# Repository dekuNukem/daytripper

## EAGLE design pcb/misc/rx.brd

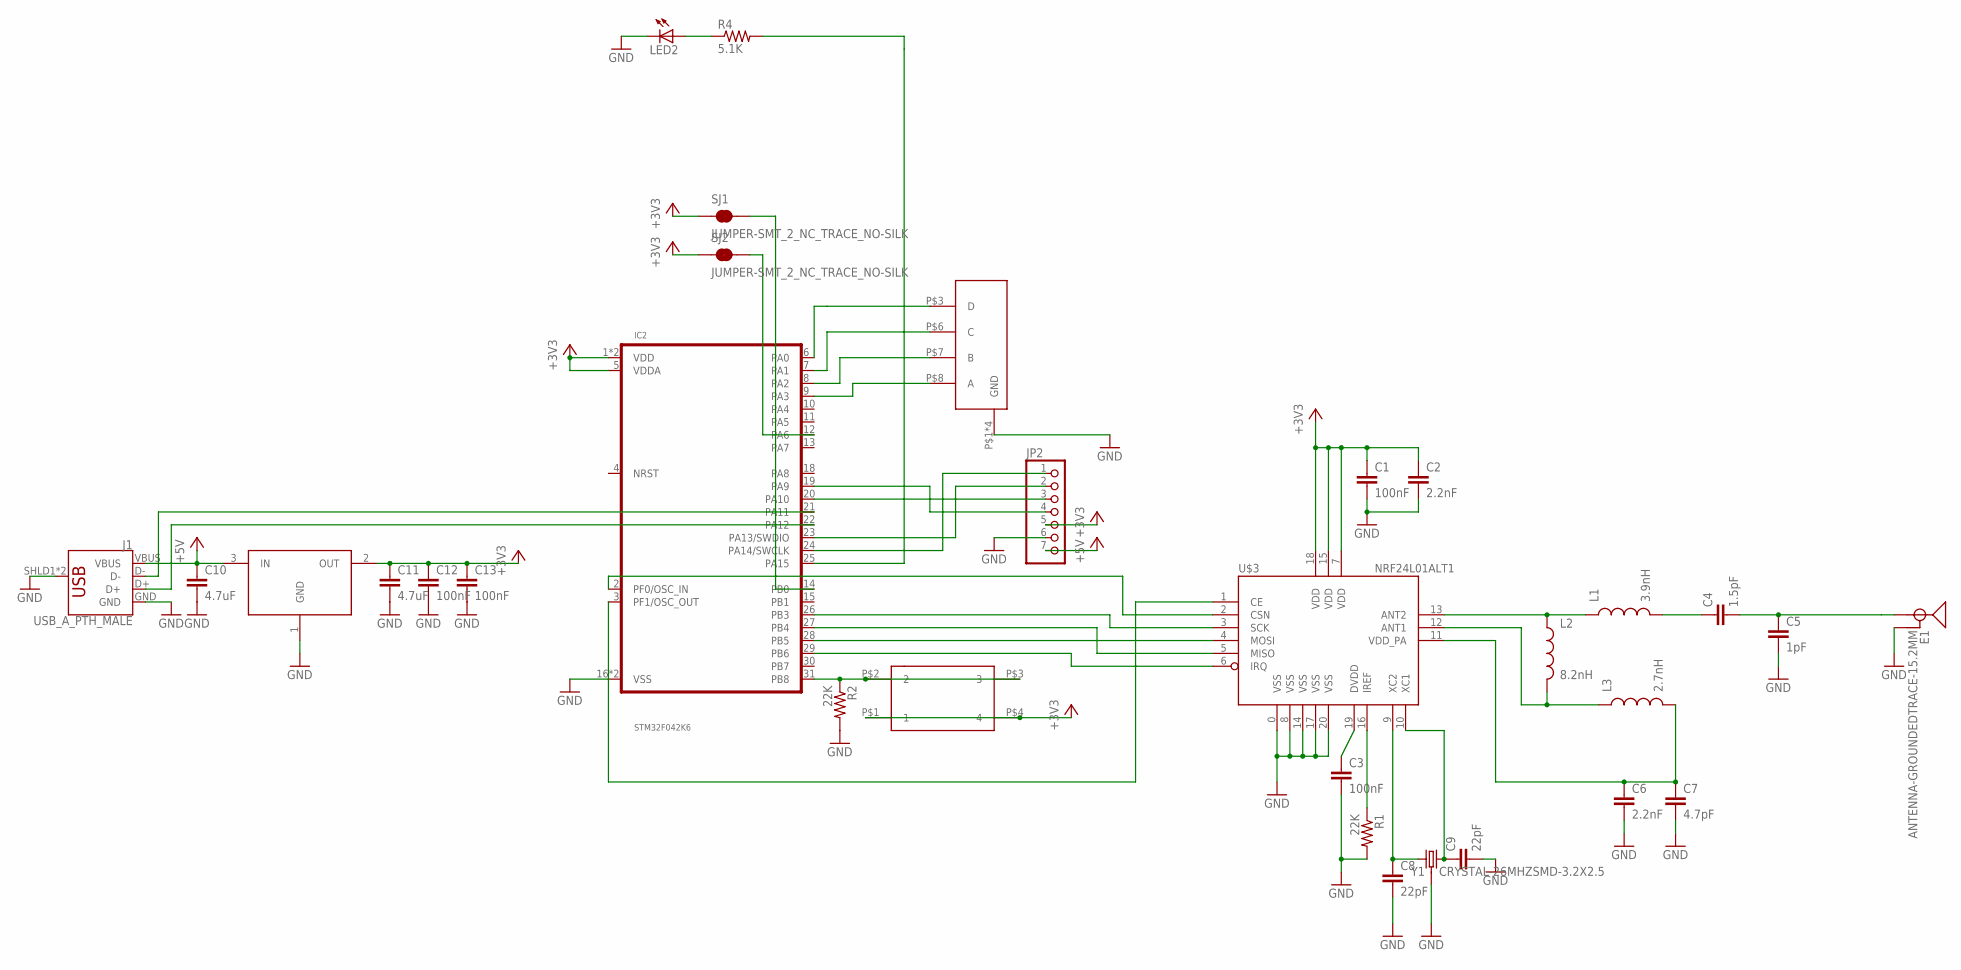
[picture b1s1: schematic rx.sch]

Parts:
C1, C3, C12, C13: 100nF; 0805
C2, C6: 2.2nF; 0805
C4: 1.5pF; 0805
C5: 1pF; 0805
C7: 4.7pF; 0805
C8, C9: 22pF; 0805
C10, C11: 4.7uF; 0805
E1: ANTENNA-GROUNDEDTRACE-15.2MM; TRACE_ANTENNA_2.4GHZ_15.2MM
IC2: STM32F042K6; TQFP32-08
J1: USB_A_PTH_MALE; USB-A-H
JP2: PINHD-1X8CLEANBIG; 1X08-CLEANBIG
L1: 3.9nH; 0805
L2: 8.2nH; 0805
L3: 2.7nH; 0805
LED2: LEDCHIP-LED0805; CHIP-LED0805
R1, R2: 22K; 0805
R4: 5.1K; 0805
SJ1, SJ2: JUMPER-SMT_2_NC_TRACE_NO-SILK; SMT-JUMPER_2_NC_TRACE_NO-SILK
U$1: SW_3POS_DEVSW_3POS_OFFICIAL; SW_3POS_FOOT_OFFICIAL
U$3: NRF24L01ALT1; QFN20_ALT1
U$4: XC6206_DEV; SOT23R_INFINEON
U$10: 324_SW; 342_SWICH_FOOT
Y1: CRYSTAL-26MHZSMD-3.2X2.5; CRYSTAL-SMD-3.2X2.5MM

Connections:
+3V3: C1.1, C2.1, C11.1, C12.1, C13.1, IC2.1 (VDD), IC2.5 (VDDA), IC2.17 (VDD), JP2.5, SJ1.1, SJ2.1, U$3.7 (VDD), U$3.15 (VDD), U$3.18 (VDD), U$4.2 (OUT), U$10.P$1 (1), U$10.P$4 (4)
+5V: C10.1, J1.VBUS, JP2.7, U$4.3 (IN)
GND: C1.2, C2.2, C3.2, C5.2, C6.2, C7.2, C8.2, C9.2, C10.2, C11.2, C12.2, C13.2, E1.GND, IC2.16 (VSS), IC2.32 (VSS), J1.GND, J1.SHLD1 (SHIELD), J1.SHLD2 (SHIELD), JP2.6, LED2.C, R1.2, R2.2, U$1.P$1 (GND), U$1.P$2 (GND), U$1.P$4 (GND), U$1.P$5 (GND), U$3.0 (VSS), U$3.8 (VSS), U$3.14 (VSS), U$3.17 (VSS), U$3.20 (VSS), U$4.1 (GND), Y1.2 (3), Y1.4 (3)
unnamed: C3.1, U$3.19 (DVDD)
unnamed: R1.1, U$3.16 (IREF)
unnamed: L1.1, L2.1, U$3.13 (ANT2)
unnamed: C4.1, L1.2
unnamed: C4.2, C5.1, E1.ANT (SIGNAL)
unnamed: L2.2, L3.1, U$3.12 (ANT1)
unnamed: C8.1, U$3.9 (XC2), Y1.1
unnamed: C6.1, C7.1, L3.2, U$3.11 (VDD_PA)
unnamed: C9.1, U$3.10 (XC1), Y1.3 (2)
unnamed: IC2.6 (PA0), U$1.P$3 (D)
unnamed: IC2.31 (PB8), R2.1, U$10.P$2 (2), U$10.P$3 (3)
unnamed: IC2.21 (PA11), J1.D-
unnamed: IC2.22 (PA12), J1.D+
unnamed: IC2.28 (PB5), U$3.4 (MOSI)
unnamed: IC2.27 (PB4), U$3.5 (MISO)
unnamed: IC2.26 (PB3), U$3.3 (SCK)
unnamed: IC2.29 (PB6), U$3.6 (IRQ)
unnamed: LED2.A, R4.1
unnamed: IC2.2 (PF0/OSC_IN), U$3.2 (CSN)
unnamed: IC2.3 (PF1/OSC_OUT), U$3.1 (CE)
unnamed: IC2.24 (PA14/SWCLK), JP2.1
unnamed: IC2.23 (PA13/SWDIO), JP2.2
unnamed: IC2.20 (PA10), JP2.3
unnamed: IC2.19 (PA9), JP2.4
unnamed: IC2.7 (PA1), U$1.P$6 (C)
unnamed: IC2.8 (PA2), U$1.P$7 (B)
unnamed: IC2.9 (PA3), U$1.P$8 (A)
unnamed: IC2.25 (PA15), R4.2
unnamed: IC2.12 (PA6), SJ2.2
unnamed: IC2.14 (PB0), SJ1.2

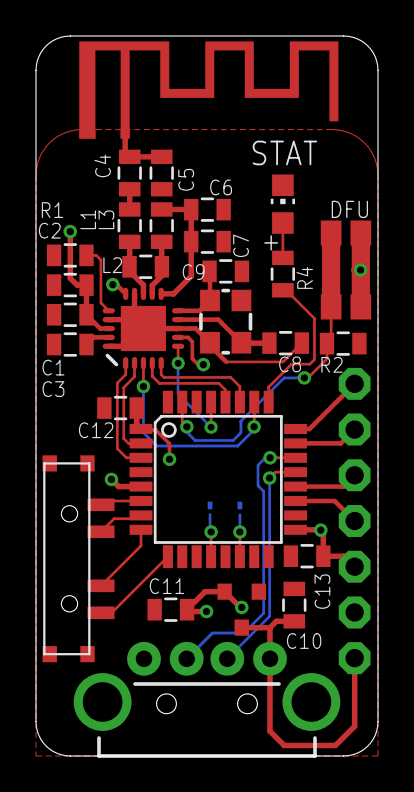
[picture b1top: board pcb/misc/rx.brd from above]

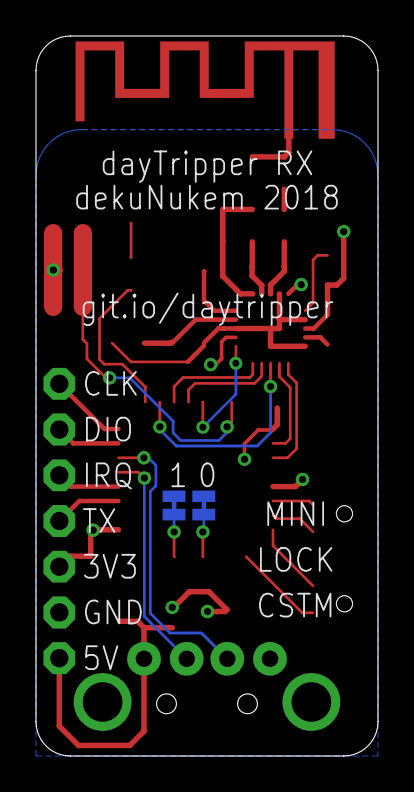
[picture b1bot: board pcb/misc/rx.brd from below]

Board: 2 copper layers, 19.0 x 40.0 mm, 31 parts (2 on the bottom side), 33 nets.

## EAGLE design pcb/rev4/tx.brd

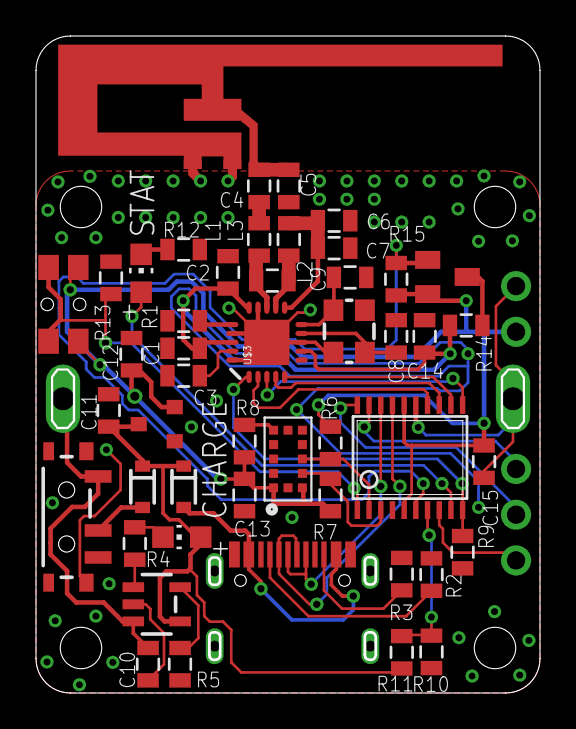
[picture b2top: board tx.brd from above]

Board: 2 copper layers, 28.0 x 36.5 mm, 55 parts (1 on the bottom side), 40 nets.

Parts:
BT1: TX_SPARKFUN-BATTERIES_BATTCON_24.5MM_PTH
C1, C2, C10, C11, C12, C14: 4.7uF; 0805
C3, C13, C15: 100nF; 0805
C4: 1.5pF; 0805
C5: 1pF; 0805
C6: 2.2nF; 0805
C7: 4.7pF; 0805
C8, C9: 22pF; 0805
D1, D2: BAT20J; SOD-323
E1: ANTENNA; TRACE_ANTENNA_2.4GHZ_25.7MM_TUNED
JP1: 1X03-CLEANBIG
L1: 3.9nH; 0805
L2: 8.2nH; 0805
L3: 2.7nH; 0805
LED1, LED2: CHIP-LED0805
Q1: BSS84; SOT23
R1, R5, R8, R9, R10, R11, R13, R15: 22K; 0805
R2, R3, R4, R6, R7, R12: 5.1K; 0805
R14: 1 Ohm; 0805
S2: SWITCH-SPST-SMD-A
U1: LGA12_ST
U3: MCP73831T-2ACI/OT; SOT23-5
U$1, U$12, U$13, U$14: M2_SCREW_DEV; M2_SCREW_FOOT
U$2: STM32F030F4; TSSOP20
U$3: NRF24L01ALT1; QFN20_ALT1
U$4: USBC_16P; USBC_16P_FOOT
U$9: XC6206_DEV; SOT23R_INFINEON
U$10: 324_SW324_SWITCH_FOOT_HOLE; 342_SWICH_FOOT_HOLE
U$11: PINHD1X2; 1X02
Y1: CRYSTAL-26MHZSMD-3.2X2.5; CRYSTAL-SMD-3.2X2.5MM

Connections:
+3V3: C12.1, C13.1, C15.1, Q1.2, R6.2, R7.2, R8.2, R15.1, U1.1, U1.11, U$2.5, U$2.16, U$9.2, U$10.P$1, U$10.P$4, U$11.1
GND: BT1.2, C1.2, C2.2, C3.2, C5.2, C6.2, C7.2, C8.2, C9.2, C10.2, C11.2, C12.2, C13.2, C14.2, C15.2, E1.GND, E1.GND2, R1.2, R2.2, R3.2, R5.2, R9.2, R11.1, R12.1, R13.2, S2.G1, S2.G2, S2.G3, S2.G4, U1.2, U1.3, U1.4, U1.6, U1.12, U3.2, U$2.15, U$3.0, U$3.8, U$3.14, U$3.17, U$3.20, U$4.A1B12, U$4.B11A12, U$4.P$13, U$4.P$14, U$4.P$15, U$4.P$16, U$9.1, U$11.2, Y1.2, Y1.4
unnamed: C3.1, U$3.19
unnamed: R1.1, U$3.16
unnamed: L1.1, L2.1, U$3.13
unnamed: C4.1, L1.2
unnamed: C4.2, C5.1, E1.ANT
unnamed: L2.2, L3.1, U$3.12
unnamed: C8.1, U$3.9, Y1.1
unnamed: C6.1, C7.1, L3.2, U$3.11
unnamed: C9.1, U$3.10, Y1.3
unnamed: R3.1, U$4.B5
unnamed: R2.1, U$4.A5
unnamed: LED1.C, R4.1
unnamed: R4.2, U3.1
unnamed: U$2.13, U$3.4
unnamed: U$2.12, U$3.5
unnamed: U$2.11, U$3.3
unnamed: R5.1, U3.5
unnamed: U$2.18, U$4.A6, U$4.B6
unnamed: D2.A, S2.2
unnamed: U$2.14, U$3.2
unnamed: R9.1, U$2.10, U$3.1
unnamed: R7.1, U1.10, U$2.3
unnamed: R6.1, U1.9, U$2.2
unnamed: R8.1, U1.5
unnamed: BT1.1, C10.1, S2.3, U3.3
unnamed: D1.A, U$4.A4B9, U$4.B4A9
unnamed: C11.1, D1.C, D2.C, LED1.A, R10.2, U3.4, U$9.3
unnamed: LED2.C, R12.2
unnamed: LED2.A, U$2.9
unnamed: R13.1, U$2.1, U$10.P$2, U$10.P$3
unnamed: JP1.3, U$2.19
unnamed: JP1.2, U$2.20
unnamed: JP1.1, U$2.8
unnamed: U$2.17, U$4.A7, U$4.B7
unnamed: R10.1, R11.2, U$2.7
unnamed: C1.1, C2.1, C14.1, R14.2, U$3.7, U$3.15, U$3.18
unnamed: Q1.3, R14.1
unnamed: Q1.1, R15.2, U$2.6

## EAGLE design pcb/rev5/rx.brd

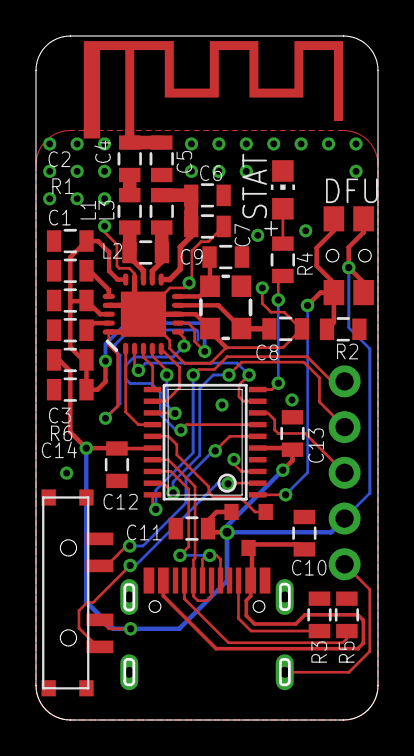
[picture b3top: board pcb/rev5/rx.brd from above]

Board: 2 copper layers, 19.0 x 38.0 mm, 34 parts (1 on the bottom side), 32 nets.

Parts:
C1, C2, C10, C11, C14: 4.7uF; 0805
C3, C12, C13: 100nF; 0805
C4: 1.5pF; 0805
C5: 1pF; 0805
C6: 2.2nF; 0805
C7: 4.7pF; 0805
C8, C9: 12pF; 0805
E1: ANTENNA-GROUNDEDTRACE-15.2MM; TRACE_ANTENNA_2.4GHZ_15.2MM
IC1: STM32F042F4; TSSOP20
IC2: NRF24L01ALT1; QFN20_ALT1
L1: 3.9nH; 0805
L2: 8.2nH; 0805
L3: 2.7nH; 0805
LED1: CHIP-LED0805
R1, R2: 22K; 0805
R3, R4, R5: 5.1K; 0805
R6: 1 Ohm; 0805
SW1: SW_3POS_DEVSW_3POS_OFFICIAL; SW_3POS_FOOT_OFFICIAL
SW2: 324_SW324_SWITCH_FOOT_HOLE; 342_SWICH_FOOT_HOLE
TP2: TPTP12R; TP12R
U1: USBC_16P; USBC_16P_FOOT
U2: XC6206_DEV; SOT23R_INFINEON
U$5: PINHD5; 1X05
Y1: 16MHz_12pF; CRYSTAL-SMD-3.2X2.5MM

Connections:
+3V3: C11.1, C12.1, C13.1, IC1.5, IC1.16, R6.1, SW1.P$7, SW2.P$1, SW2.P$4, U2.2, U$5.4
+5V: C10.1, U1.A4B9, U1.B4A9, U2.3
GND: C1.2, C2.2, C3.2, C5.2, C6.2, C7.2, C8.2, C9.2, C10.2, C11.2, C12.2, C13.2, C14.2, E1.GND, IC1.15, IC2.0, IC2.8, IC2.14, IC2.17, IC2.20, LED1.C, R1.2, R2.2, R3.2, R5.2, SW1.P$1, SW1.P$2, SW1.P$4, SW1.P$5, U1.A1B12, U1.B11A12, U1.P$13, U1.P$14, U1.P$15, U1.P$16, U2.1, U$5.5, Y1.2, Y1.4
unnamed: C3.1, IC2.19
unnamed: IC2.16, R1.1
unnamed: IC2.13, L1.1, L2.1
unnamed: C4.1, L1.2
unnamed: C4.2, C5.1, E1.ANT
unnamed: IC2.12, L2.2, L3.1
unnamed: C8.1, IC2.9, Y1.1
unnamed: C6.1, C7.1, IC2.11, L3.2
unnamed: C9.1, IC2.10, Y1.3
unnamed: IC1.2, SW1.P$8
unnamed: IC1.1, R2.1, SW2.P$2, SW2.P$3
unnamed: IC1.17, U1.A7, U1.B7
unnamed: IC1.18, U1.A6, U1.B6
unnamed: IC1.12, IC2.5
unnamed: IC1.13, IC2.4
unnamed: IC1.11, IC2.3
unnamed: IC1.19, U$5.2
unnamed: LED1.A, R4.1
unnamed: IC1.3, TP2.TP
unnamed: IC1.20, U$5.1
unnamed: IC1.8, U$5.3
unnamed: IC1.14, IC2.1
unnamed: IC1.10, R4.2
unnamed: IC1.9, IC2.2
unnamed: R3.1, U1.B5
unnamed: IC1.6, SW1.P$6
unnamed: R5.1, U1.A5
unnamed: C1.1, C2.1, C14.1, IC2.7, IC2.15, IC2.18, R6.2
unnamed: IC1.7, IC2.6

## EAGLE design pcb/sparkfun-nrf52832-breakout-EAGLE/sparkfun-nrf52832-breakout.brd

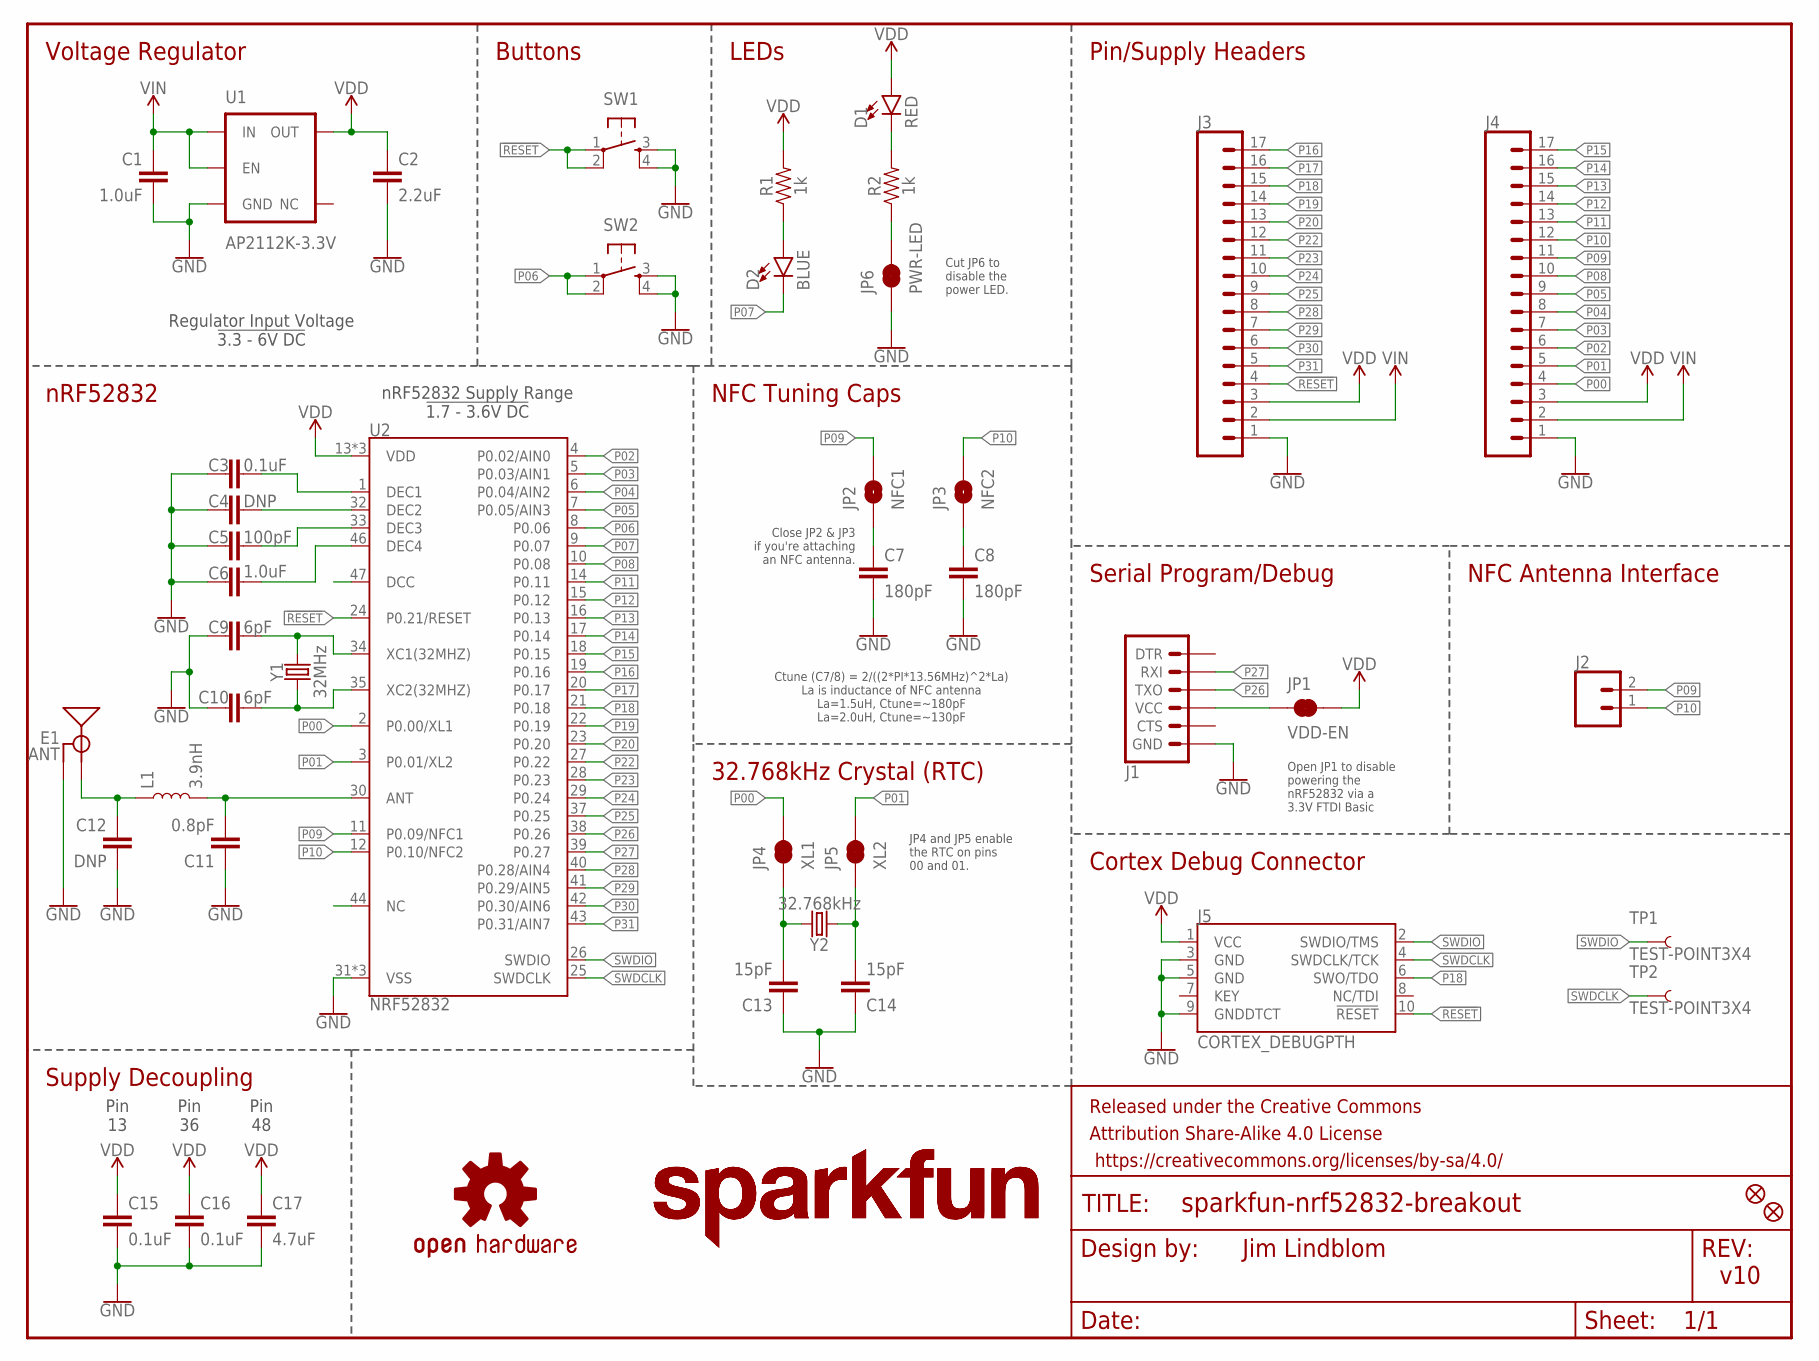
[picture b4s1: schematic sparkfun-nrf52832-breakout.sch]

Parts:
C1: 1.0uF; 0603
C2: 2.2uF; 0603
C3, C15, C16: 0.1uF; 0402
C4, C12: DNP; 0402
C5: 100pF; 0402
C6: 1.0uF; 0402
C7, C8: 180pF; 0603
C9, C10: 6pF; 0402
C11: 0.8pF; 0402
C13, C14: 15pF; 0402
C17: 4.7uF; 0603
D1: RED; LED-0603
D2: BLUE; LED-0603
E1: ANT; TRACE_ANTENNA_2.4GHZ_15.2MM
FD1, FD2: FIDUCIALUFIDUCIAL; FIDUCIAL-MICRO
FRAME1: FRAME-LETTER; CREATIVE_COMMONS
J1: ARDUINO_SERIAL_PROGRAMPTH; 1X06
J2: CONN_02PTH; 1X02
J3, J4: CONN_17; 1X17
J5: CORTEX_DEBUGPTH; 2X5-PTH-1.27MM
JP1: VDD-EN; SMT-JUMPER_2_NC_TRACE_SILK
JP2: NFC1; SMT-JUMPER_2_NO_SILK
JP3: NFC2; SMT-JUMPER_2_NO_SILK
JP4: XL1; PAD-JUMPER-2-NC_BY_TRACE_YES_SILK
JP5: XL2; PAD-JUMPER-2-NC_BY_TRACE_YES_SILK
JP6: PWR-LED; PAD-JUMPER-2-NC_BY_TRACE_YES_SILK
L1: 3.9nH; 0402
LOGO1: OSHW-LOGOMINI; OSHW-LOGO-MINI
LOGO2, LOGO3: SFE_LOGO_NAME.1_INCH; SFE_LOGO_NAME_.1
R1, R2: 1k; 0603
SW1, SW2: SWITCH_SPST_4_PINRECT; TACTILE_SWITCH_SMD_4.6X2.8MM
TP1, TP2: TEST-POINT3X4; PAD.03X.04
U1: AP2112K-3.3V; SOT23-5
U2: NRF52832; QFN48-6X6MM
Y1: 32MHz; CRYSTAL-SMD-2.0X1.6MM
Y2: 32.768kHz; CRYSTAL-SMD-3.2X1.5MM

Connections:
!RESET!: J3.4, J5.10 (!RESET), SW1.1, SW1.2, U2.24 (P0.21/RESET)
ANT: C11.2, L1.2, U2.30 (ANT)
DCC: U2.47 (DCC)
DEC1: C3.2, U2.1 (DEC1)
DEC2: C4.2, U2.32 (DEC2)
DEC3: C5.2, U2.33 (DEC3)
DEC4: C6.2, U2.46 (DEC4)
GND: C1.2, C2.2, C3.1, C4.1, C5.1, C6.1, C7.2, C8.2, C9.1, C10.2, C11.1, C12.2, C13.1, C14.1, C15.2, C16.2, C17.2, E1.GND, J1.6 (GND), J3.1, J4.1, J5.3 (GND), J5.5 (GND), J5.9 (GNDDTCT), JP6.1, SW1.3, SW1.4, SW2.3, SW2.4, U1.2 (GND), U2.31 (VSS), U2.45 (VSS), U2.EP (VSS)
unnamed: JP6.2, R2.1
unnamed: C13.2, JP4.1, Y2.P$2 (2)
unnamed: C14.2, JP5.1, Y2.P$1 (1)
unnamed: C12.1, E1.ANT (SIGNAL), L1.1
unnamed: D1.C, R2.2
unnamed: J1.4 (VCC), JP1.1
unnamed: D2.A, R1.1
NC: U2.44 (NC)
NFC1: C7.1, JP2.1
NFC2: C8.1, JP3.1
P00: J4.4, JP4.2, U2.2 (P0.00/XL1)
P01: J4.5, JP5.2, U2.3 (P0.01/XL2)
P02: J4.6, U2.4 (P0.02/AIN0)
P03: J4.7, U2.5 (P0.03/AIN1)
P04: J4.8, U2.6 (P0.04/AIN2)
P05: J4.9, U2.7 (P0.05/AIN3)
P06: SW2.1, SW2.2, U2.8 (P0.06)
P07: D2.C, U2.9 (P0.07)
P08: J4.10, U2.10 (P0.08)
P09: J2.2, J4.11, JP2.2, U2.11 (P0.09/NFC1)
P10: J2.1, J4.12, JP3.2, U2.12 (P0.10/NFC2)
P11: J4.13, U2.14 (P0.11)
P12: J4.14, U2.15 (P0.12)
P13: J4.15, U2.16 (P0.13)
P14: J4.16, U2.17 (P0.14)
P15: J4.17, U2.18 (P0.15)
P16: J3.17, U2.19 (P0.16)
P17: J3.16, U2.20 (P0.17)
P18: J3.15, J5.6 (SWO/TDO), U2.21 (P0.18)
P19: J3.14, U2.22 (P0.19)
P20: J3.13, U2.23 (P0.20)
P22: J3.12, U2.27 (P0.22)
P23: J3.11, U2.28 (P0.23)
P24: J3.10, U2.29 (P0.24)
P25: J3.9, U2.37 (P0.25)
P26: J1.3 (TXO), U2.38 (P0.26)
P27: J1.2 (RXI), U2.39 (P0.27)
P28: J3.8, U2.40 (P0.28/AIN4)
P29: J3.7, U2.41 (P0.29/AIN5)
P30: J3.6, U2.42 (P0.30/AIN6)
P31: J3.5, U2.43 (P0.31/AIN7)
SWDCLK: J5.4 (SWDCLK/TCK), TP2.P$1, U2.25 (SWDCLK)
SWDIO: J5.2 (SWDIO/TMS), TP1.P$1, U2.26 (SWDIO)
VDD: C2.1, C15.1, C16.1, C17.1, D1.A, J3.3, J4.3, J5.1 (VCC), JP1.2, R1.2, U1.5 (OUT), U2.13 (VDD), U2.36 (VDD), U2.48 (VDD)
VIN: C1.1, J3.2, J4.2, U1.1 (IN), U1.3 (EN)
XC1: C9.2, U2.34 (XC1(32MHZ)), Y1.3 (2)
XC2: C10.1, U2.35 (XC2(32MHZ)), Y1.1

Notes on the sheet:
Pin 13
Pin 36
Pin 48
v10
Jim Lindblom
Ctune (C7/8) = 2/((2*PI*13.56MHz)^2*La) La is inductance of NFC antenna La=1.5uH, Ctune=~180pF La=2.0uH, Ctune=~130pF
Voltage Regulator
Buttons
LEDs
Pin/Supply Headers
nRF52832
32.768kHz Crystal (RTC)
Supply Decoupling
NFC Tuning Caps
Cortex Debug Connector
Serial Program/Debug
NFC Antenna Interface
Open JP1 to disable powering the nRF52832 via a 3.3V FTDI Basic
Close JP2 & JP3 if you're attaching an NFC antenna.
JP4 and JP5 enable the RTC on pins 00 and 01.
Regulator Input Voltage !3.3 - 6V DC!
nRF52832 Supply Range !1.7 - 3.6V DC!
Cut JP6 to disable the power LED.

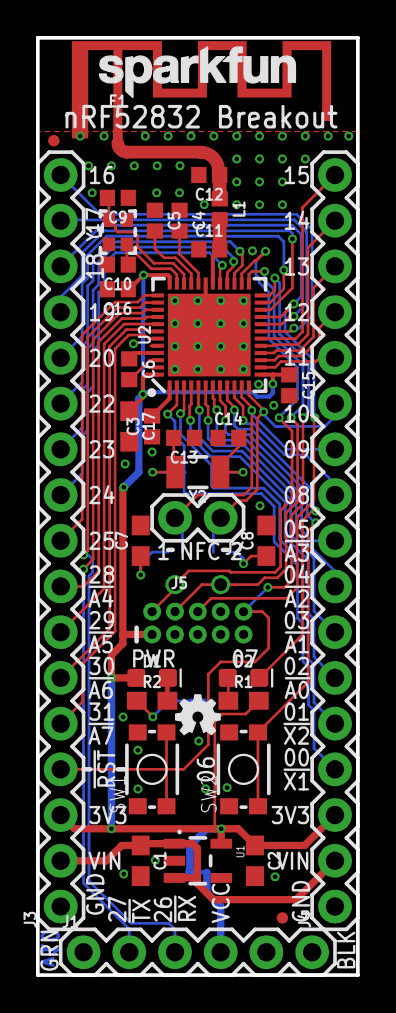
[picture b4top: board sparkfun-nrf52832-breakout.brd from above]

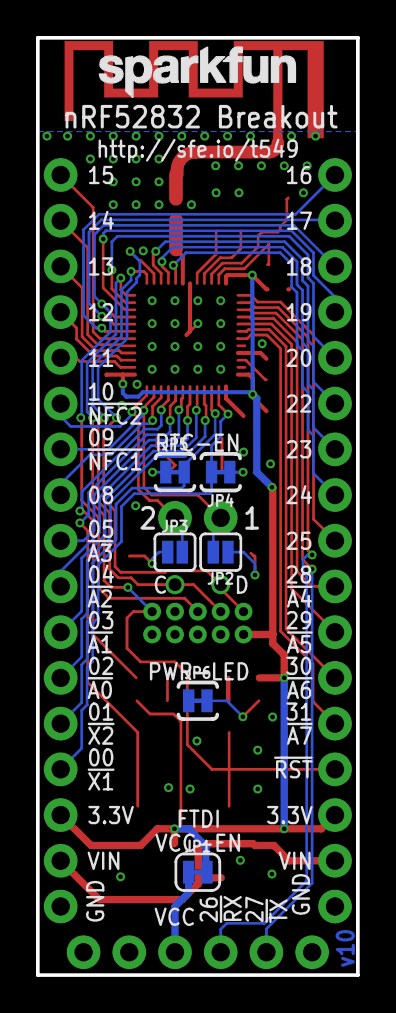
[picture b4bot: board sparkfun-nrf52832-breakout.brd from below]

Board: 2 copper layers, 17.8 x 52.1 mm, 48 parts (9 on the bottom side), 53 nets.

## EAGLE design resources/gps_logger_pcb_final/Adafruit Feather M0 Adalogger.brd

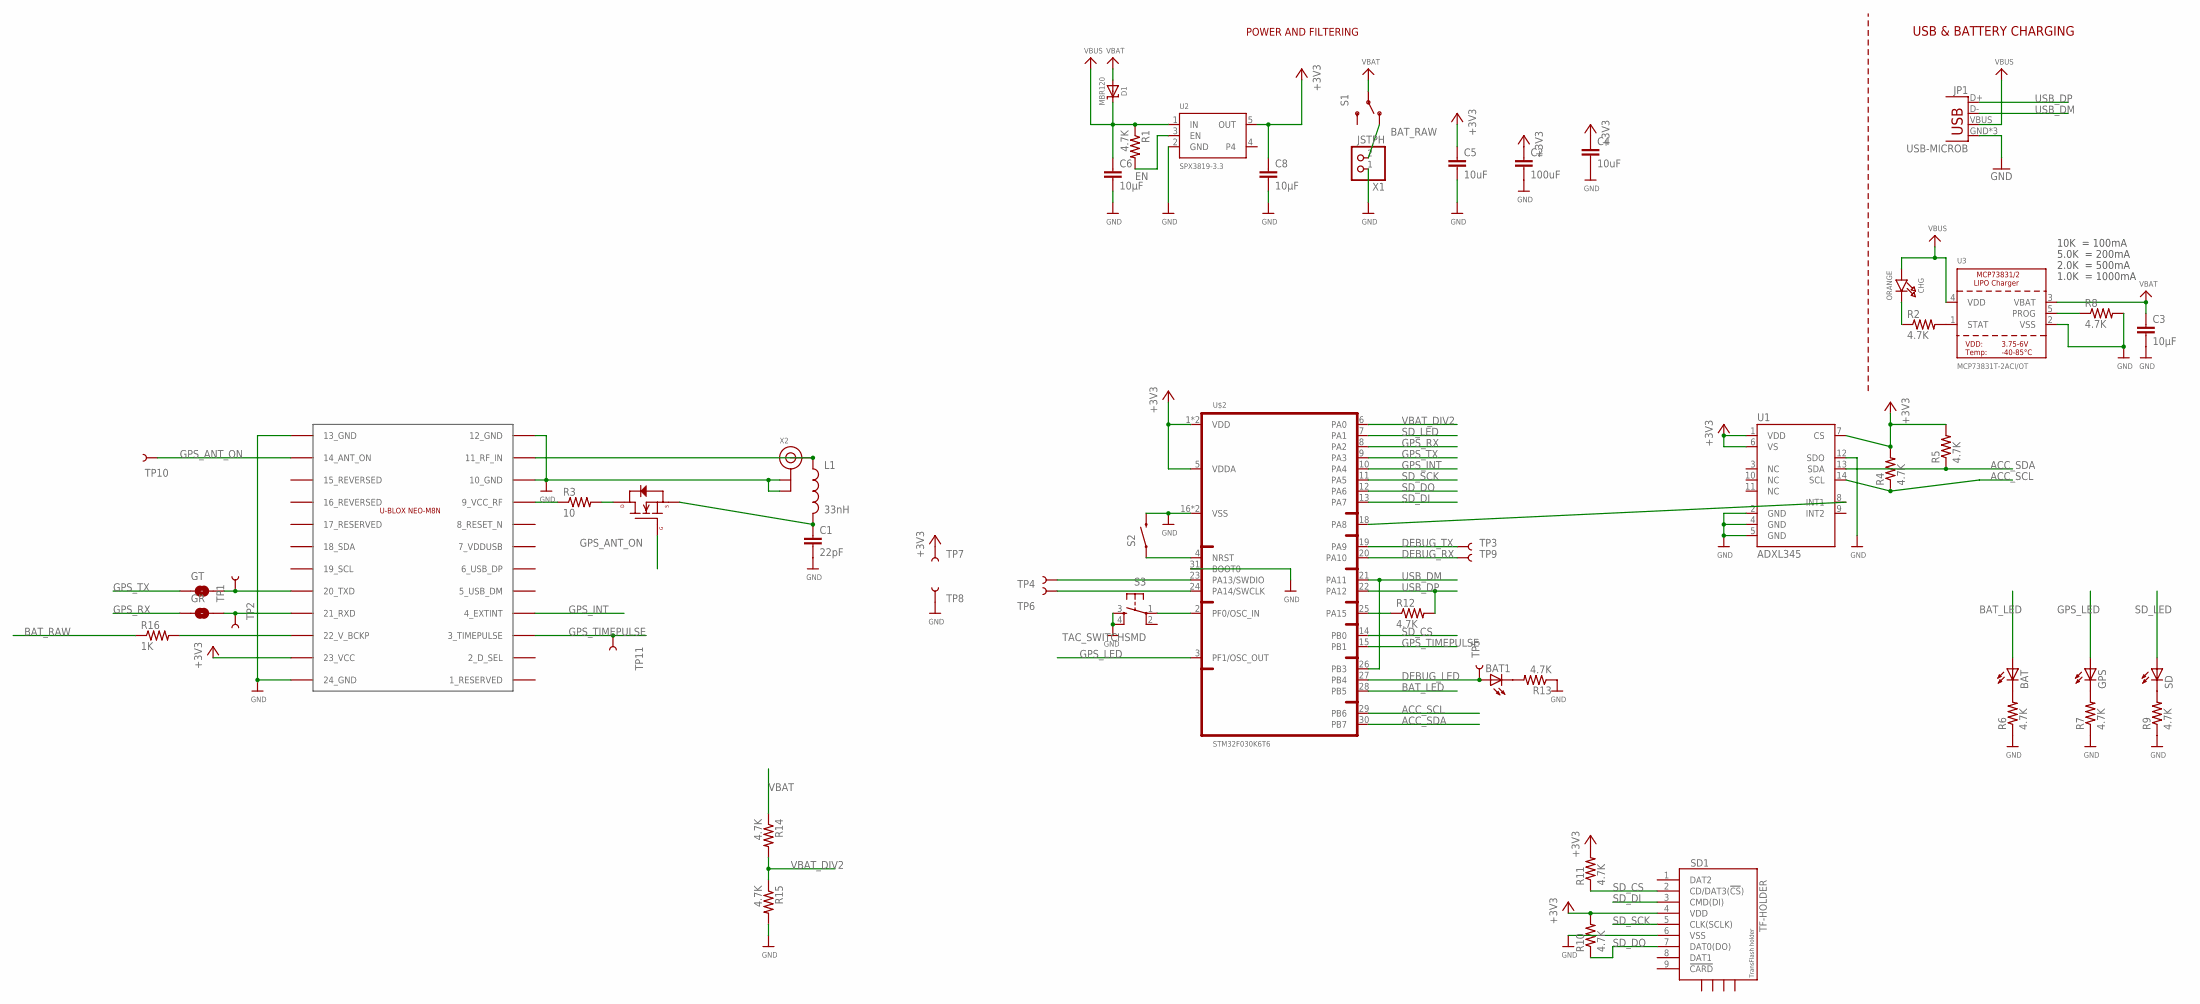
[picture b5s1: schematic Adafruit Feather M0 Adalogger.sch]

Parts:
BAT, BAT1: LEDCHIPLED_0805; CHIPLED_0805
C1: 22pF; 0805
C2: 100uF; 1210
C3, C6, C8: 10µF; 0805
C4, C5: 10uF; 0805
CHG: ORANGE; CHIPLED_0805_NOOUTLINE
D1: MBR120; SOD-123
DEKU1: UBLOX_NEO-M8N
GPS: LEDCHIPLED_0805; CHIPLED_0805
GR: JUMPER-PAD-2-NO; PAD-JUMPER-2-NO_NO_SILK
GT: JUMPER-PAD-2-NO; PAD-JUMPER-2-NO_NO_SILK
JP1: USB-MICROB
L1: 33nH; 0805
R1, R2, R4, R5, R6, R7, R8, R9, R10, R11, R12, R13, R14, R15: 4.7K; 0805
R3: 10; 0805
R16: 1K; 0805
S1: SWITCH-SPDT-SMD-A; SWITCH-SPST-SMD-A
S2: SWITCH-MOMENTARY-2TURTLE; KMR2
S3: TAC_SWITCHSMD; TACTILE-SWITCH-SMD
SD: LEDCHIPLED_0805; CHIPLED_0805
SD1: TF-HOLDER; TF-PULL
TP1, TP2, TP3, TP4, TP5, TP6, TP7, TP8, TP9, TP10, TP11: TEST-POINT3X5; PAD.03X.05
U1: ADXL345; LGA14
U2: SPX3819-3.3; SOT23-5
U3: MCP73831T-2ACI/OT; SOT23-5
U$2: STM32F030K6T6; TQFP32-08
U$24: N-CHANNEL-MOSFET-BSS138; SOT23-3
X1: JSTPH; JSTPH2
X2: ANTENNA_U.FL; U.FL

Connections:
+3V3: C2.1, C4.1, C5.1, C8.1, DEKU1.23_VCC, R4.2, R5.2, R10.2, R11.2, SD1.4 (VDD), TP7.P$1, U1.1 (VDD), U1.6 (VS), U1.7 (CS), U2.5 (OUT), U$2.1 (VDD), U$2.5 (VDDA), U$2.17 (VDD)
ACC_SCL: R4.1, U1.14 (SCL), U$2.29 (PB6)
ACC_SDA: R5.1, U1.13 (SDA), U$2.30 (PB7)
BAT_LED: BAT.A, U$2.28 (PB5)
BAT_RAW: R16.1, S1.1 (O), X1.2
DEBUG_LED: BAT1.A, TP5.P$1, U$2.27 (PB4)
DEBUG_RX: TP9.P$1, U$2.20 (PA10)
DEBUG_TX: TP3.P$1, U$2.19 (PA9)
EN: R1.2, U2.3 (EN)
GND: C1.2, C2.2, C3.2, C4.2, C5.2, C6.2, C8.2, DEKU1.10_GND, DEKU1.12_GND, DEKU1.13_GND, DEKU1.24_GND, JP1.GND, JP1.MT1 (GND), JP1.MT2 (GND), R6.1, R7.1, R8.2, R9.1, R13.1, R15.2, S2.3 (2), S3.3, S3.4, SD1.6 (VSS), TP8.P$1, U1.2 (GND), U1.4 (GND), U1.5 (GND), U1.12 (SDO), U2.2 (GND), U3.2 (VSS), U$2.16 (VSS), U$2.31 (BOOT0), U$2.32 (VSS), X1.1, X2.1 (GND), X2.2 (GND)
GPS_ANT_ON: DEKU1.14_ANT_ON, TP10.P$1, U$24.1 (G)
GPS_INT: DEKU1.4_EXTINT, U$2.10 (PA4)
GPS_LED: GPS.A, U$2.3 (PF1/OSC_OUT)
GPS_RX: GR.1, U$2.8 (PA2)
GPS_TIMEPULSE: DEKU1.3_TIMEPULSE, TP11.P$1, U$2.15 (PB1)
GPS_TX: GT.1, U$2.9 (PA3)
unnamed: CHG.C, R2.1
unnamed: DEKU1.20_TXD, GT.2, TP1.P$1
unnamed: R2.2, U3.1 (STAT)
unnamed: R8.1, U3.5 (PROG)
unnamed: DEKU1.21_RXD, GR.2, TP2.P$1
unnamed: R12.1, U$2.25 (PA15)
unnamed: S2.1, U$2.4 (NRST)
unnamed: DEKU1.11_RF_IN, L1.1, X2.3 (SIGNAL)
unnamed: R3.2, U$24.3 (D)
unnamed: C1.1, L1.2, U$24.2 (S)
unnamed: BAT.C, R6.2
unnamed: GPS.C, R7.2
unnamed: R9.2, SD.C
unnamed: S3.1, U$2.2 (PF0/OSC_IN)
unnamed: BAT1.C, R13.2
unnamed: DEKU1.22_V_BCKP, R16.2
unnamed: U1.8 (INT1), U$2.18 (PA8)
unnamed: DEKU1.9_VCC_RF, R3.1
SD_CS: R11.1, SD1.2 (CD/DAT3(!CS!)), U$2.14 (PB0)
SD_DI: SD1.3 (CMD(DI)), U$2.13 (PA7)
SD_DO: R10.1, SD1.7 (DAT0(DO)), U$2.12 (PA6)
SD_LED: SD.A, U$2.7 (PA1)
SD_SCK: SD1.5 (CLK(SCLK)), U$2.11 (PA5)
SWCLK: TP6.P$1, U$2.24 (PA14/SWCLK)
SWDIO: TP4.P$1, U$2.23 (PA13/SWDIO)
USB_DM: JP1.D-, U$2.21 (PA11), U$2.26 (PB3)
USB_DP: JP1.D+, R12.2, U$2.22 (PA12)
VBAT: C3.1, D1.A, R14.1, S1.2, U3.3 (VBAT)
VBAT_DIV2: R14.2, R15.1, U$2.6 (PA0)
VBUS: C6.1, CHG.A, D1.C, JP1.VBUS, R1.1, U2.1 (IN), U3.4 (VDD)

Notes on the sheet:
POWER AND FILTERING
10K = 100mA
5.0K = 200mA
2.0K = 500mA
1.0K = 1000mA
USB & BATTERY CHARGING

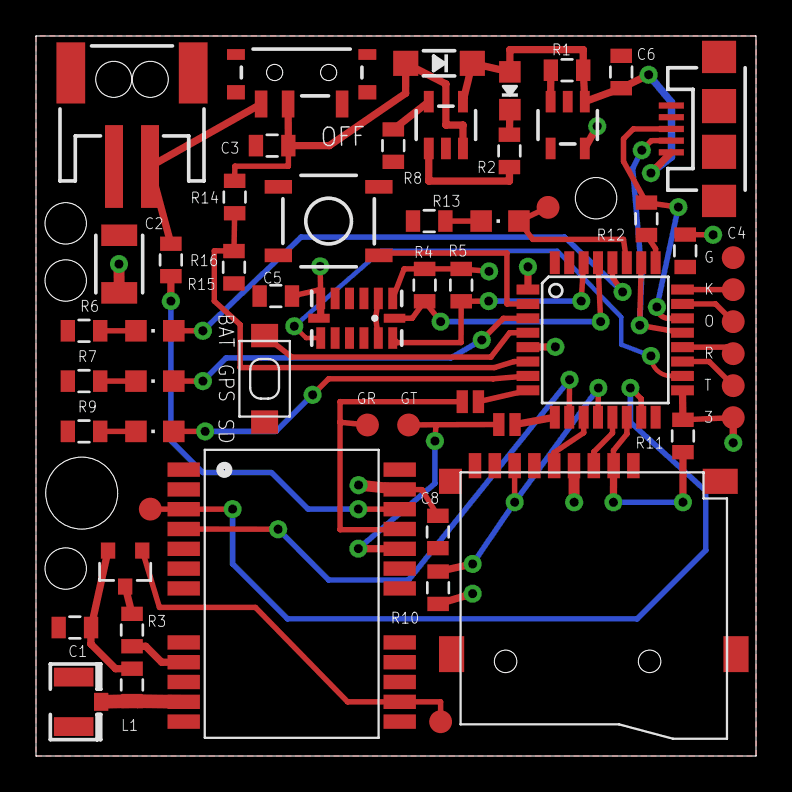
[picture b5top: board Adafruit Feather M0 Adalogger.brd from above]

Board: 2 copper layers, 40.0 x 40.0 mm, 56 parts (0 on the bottom side), 46 nets.

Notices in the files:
parts and their libraries:
SparkFun-Clocks: Licensing: Creative Commons ShareAlike 4.0 International - https://creativecommons.org/licenses/by-sa/4.0
microbuilder: This work is placed in the public domain, and may be freely used for commercial and non-commercial work with the following conditions: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
